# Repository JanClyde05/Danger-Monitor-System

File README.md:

# GPS Danger Monitor System – Full Code Documentation (v4.1)
##### BY: JAN CLYDE T. TALOSIG
##### **NEW IN v4.1: Physical Button Two-State Toggle + GPS Share / Open in Maps**
##### **NEW IN v4.0: Physical Disarm Button + False Alarm NRF Broadcast**
##### **NEW IN v3.x / Web Portal: Confirmed Accident Database + Diagnosis Notes + SOS Audio**

---

# 1. SYSTEM OVERVIEW

## 1.1 Purpose

The system is a **wearable/embedded safety monitor** that detects:

* Human falls (high confidence – three-stage FSM)
* Skid / slide events (lateral acceleration + roll rate)
* Direct high-G impacts (no freefall precondition)
* Environmental hazards (ground shock / structural instability / wave motion)

It then:

1. Gets GPS coordinates (last-known-location strategy)
2. Sends them via NRF24L01 with a token-prefixed payload
3. Triggers an SOS alert (LED + buzzer, Morse SOS pattern)
4. Opens a **web-based emergency profile with QR code quick-dial** via HID receiver
5. Allows the user to **cancel a false alarm** via physical button or web dashboard, which broadcasts a `FA,TOKEN,LAT,LNG` NRF packet to notify the receiver

---

## 1.2 System Components

### Transmitter (ESP32) – v4.1

* Sensors:
  * MPU-6050 (motion / orientation)
  * GPS module via TinyGPS++ (UART1, RX=16, TX=17)
* Communication:
  * NRF24L01 (wireless, CE=2, CSN=15)
* Interface:
  * Web dashboard in AP mode (three tabs: Monitor, Diagnostics, Simulation)
  * Physical disarm/re-arm button on GPIO 0 (BOOT button)

### Receiver (Pro Micro) – v2.3

* NRF24L01 (receiver, CE=9, CSN=10)
* HID Keyboard emulation (opens Netlify URL in browser)
* Handles three payload types: EMERGENCY, TEST, FALSE ALARM

### Web Layer

* ESP32 embedded dashboard (AP mode, 192.168.4.1)
* Netlify emergency portal (multi-page SPA with router)

---

# 2. ABSTRACT PROGRAM FLOW (SUMMARY)

## HIGH-LEVEL FLOW

```
BOOT → INIT HARDWARE → CALIBRATION → RUN LOOP
         ↓
     READ SENSORS (IMU + GPS)
         ↓
    APPLY SIM OVERRIDE (if drill mode)
         ↓
  UPDATE FALL-IMPACT-STILLNESS FSM
         ↓
  CHECK SKID / DIRECT IMPACT DETECTORS
         ↓
  CHECK ENVIRONMENTAL ANALYSIS (every 1 s)
         ↓
  SEND NRF ALERT + SOS (if triggered)
         ↓
  POLL PHYSICAL BUTTON (two-state toggle)
         ↓
  UPDATE WEB UI + BURST TEST (non-blocking)
         ↓
       REPEAT
```

---

## CORE LOGIC PIPELINES

### FALL DETECTION PIPELINE

```
[FS_IDLE]
   ↓ A_m < 0.40 g
[FS_FREEFALL]
   ↓ sustained ≥ 100 ms
[FS_WAIT_IMPACT]
   ↓ A_m > 3.00 g within 500 ms
[FS_STILLNESS]
   ↓ σ(A_m) < 0.15 g over 2 s
[FS_CONFIRMED → ALERT]
```

All stages must pass — eliminates false positives from jumping, device drops, or sleeping.

---

### SECONDARY DETECTORS (Parallel to FSM)

```
SKID / SLIDE:
  ay > 2.0 g  AND  gx > 330 °/s  sustained ≥ 200 ms
  → Ref: motorcycle crash paper, 96% accuracy

DIRECT IMPACT:
  A_m spike > 4.50 g  (no freefall precondition)
  5 s debounce between events
  → Ref: construction-site LF falls 4–9 g (Sensors 2022)
```

---

### EMERGENCY RESPONSE PIPELINE

```
[ACCIDENT DETECTED]
   ↓
[NRF PAYLOAD: "TOKEN,LAT,LNG"]
   ↓
[RECEIVER HID TRIGGERS URL]
   ↓
[NETLIFY PROFILE PAGE OPENS]
   ↓
[MEDICAL INFO + QR CODE DISPLAYED]
   ↓
[RESPONDER SCANS QR → tel: DIALS CONTACT]
   ↓ (optional)
[RESPONDER CONFIRMS ACCIDENT → DATABASE ENTRY]
```

---

### FALSE ALARM CANCELLATION PIPELINE (v4.0+)

```
[ALERT ACTIVE]
   ↓ (user presses physical button OR web False Alarm button)
[stopSOSAlert() — LED/buzzer off]
   ↓
[nrfSendFalseAlarm(): "FA,TOKEN,LAT,LNG"]
   ↓
[RECEIVER HID TRIGGERS FALSE ALARM URL]
   ↓
[NETLIFY: green "USER IS SAFE" page]
   ↓
[RESCUER INFORMED — NO RESPONSE NEEDED]
```

---

# 3. DETAILED MODULE EXPLANATION

## 3.1 SETUP PHASE

```
setup():
  Start Serial (115200)
  Start GPS UART1 (9600 baud, RX=16, TX=17)
  Initialize I2C (Wire.begin)
  Wake MPU-6050 (write 0x00 to PWR_MGMT_1)
  Calibrate MPU (3 seconds, 200 samples)
  Record gpsSearchStart timestamp
  Start WiFi AP (SSID: "GPS Danger Monitor", open, IP: 192.168.4.1)
  Initialize NRF24 (CE=2, CSN=15, PA_HIGH, 32-byte payload)
  Register all WebServer routes
  Configure GPIO: LED (4), Buzzer (5), Button (0 INPUT_PULLUP)
```

---

## 3.2 MAIN LOOP STRUCTURE

```
loop():
  Compute delta time dt
  server.handleClient()
  Poll physical button (50 ms debounce, two-state toggle)
  Run NRF burst test step (non-blocking, if pending)
  Feed GPS bytes → TinyGPS++, update hasFix / lastLat / lastLng
  readMPU() → apply sim override → updateOrientation(dt)
  Compute A_m = sqrt(ax²+ay²+az²)
  pushEnvSample(A_m, roll, pitch)
  Run Fall-Impact-Stillness FSM (if armed)
  Run Skid detector (if armed, FSM idle)
  Run Direct-Impact detector (if armed, FSM idle, not in skid)
  Environmental analysis (every 1 s, if armed, not sim)
  Drive SOS pattern (non-blocking)
```

---

# 4. SENSOR PROCESSING

## 4.1 MPU DATA FLOW

```
Raw MPU Data → Bias Removal → Physical Units → Orientation Estimation
```

### readMPU()

* Reads 14 bytes from register 0x3B
* Extracts ax, ay, az (±2 g range → /16384) and gx, gy, gz (±250 °/s → /131)
* Subtracts calibration offsets

### calibrateMPU()

* 200 samples over CALIB_MS (3000 ms)
* Averages each axis; subtracts 1.0 g from az bias (gravity)
* Stores: aBiasX/Y/Z, gBiasX/Y/Z

### updateOrientation(dt)

Complementary filter (α = 0.02):

```
aRoll  = atan2(ay, az) × 57.296°
aPitch = atan2(-ax, √(ay²+az²)) × 57.296°

roll  = (1-α)×(roll  + gx×dt) + α×aRoll
pitch = (1-α)×(pitch + gy×dt) + α×aPitch
```

## 4.2 ACCELERATION MAGNITUDE

```
A_m = sqrt(ax² + ay² + az²)
```

Orientation-independent scalar used by all detection stages.

---

# 5. FALL DETECTION STATE MACHINE

## States

| State           | Meaning                           |
|-----------------|-----------------------------------|
| FS_IDLE         | Normal monitoring                 |
| FS_FREEFALL     | Low-gravity condition detected    |
| FS_WAIT_IMPACT  | Waiting for impact spike          |
| FS_STILLNESS    | Verifying post-impact unconscious |
| FS_CONFIRMED    | Alert triggered                   |

## Full Flowchart

```
FS_IDLE
  IF A_m < 0.40 g → FS_FREEFALL, start timer

FS_FREEFALL
  IF A_m ≥ 0.40 g → back to FS_IDLE (false trigger)
  IF duration ≥ 100 ms → FS_WAIT_IMPACT
    Record fallStartMs, increment fallEventCount

FS_WAIT_IMPACT
  IF A_m > 3.00 g → FS_STILLNESS, reset stillness buffer
  IF timeout > 500 ms → FS_IDLE, increment fallCancelCount

FS_STILLNESS
  Collect samples for 2000 ms
  Compute σ(A_m)
  IF σ < 0.15 g → FS_CONFIRMED
  ELSE          → FS_IDLE (user conscious), increment fallCancelCount

FS_CONFIRMED
  Increment fallConfirmCount
  Log response time (now − fallStartMs)
  IF !simMode → nrfSendCoords(lastLat, lastLng, "Fall confirmed")
  ELSE        → nrfSendTest(99, "SIMFALL")
  startSOSAlert()
  → FS_IDLE
```

## Why This Works (Thesis Logic)

* Freefall alone → jumping false positive
* Impact alone → dropping the device
* Stillness alone → user sleeping
* **Combination of all three = confirmed real accident**

---

# 6. SECONDARY DETECTORS

## 6.1 Skid / Slide Detector

Active when: `armed == true` AND `fallState == FS_IDLE`

```
Condition: fabsf(ay) > 2.0 g  AND  fabsf(gx) > 330 °/s

If condition holds:
  Start skid timer on first detection
  If sustained ≥ 200 ms:
    skidCount++
    nrfSendCoords() OR nrfSendTest (sim)
    startSOSAlert()
    inSkid = false (reset)

If condition breaks before 200 ms:
  inSkid = false (cancel)
```

Reference: motorcycle crash paper, lateral 0.70 g + roll rate criteria, 96% accuracy.
*(Note: firmware thresholds are set higher — 2.0 g / 330 °/s — for reduced false positives in the specific deployment scenario.)*

---

## 6.2 Direct Impact Detector

Active when: `armed == true` AND `fallState == FS_IDLE` AND `!inSkid`

```
Condition: A_m > 4.50 g  AND  (now − lastImpactAlert) > 5000 ms

  lastImpactAlert = now
  impactCount++
  nrfSendCoords() OR nrfSendTest (sim)
  startSOSAlert()
```

Reference: Sensors 2022 — low-floor fall studies, 4–9 g impact range.

---

## 6.3 Environmental / Structural Instability

Runs every 1000 ms using the last `bufCount` samples from the rolling buffer (max 50).

```
sMag   = stddev(magBuf)
sRoll  = stddev(rollBuf)
sPitch = stddev(pitchBuf)

groundShock:  sMag ≥ 0.40  AND  sRoll < 10.0  AND  sPitch < 10.0
waveMotion:   sMag ≥ 0.24  AND  (sRoll ≥ 10.0 OR sPitch ≥ 10.0)

IF groundShock → nrfSendCoords("Ground shock")   + startSOSAlert()
IF waveMotion  → nrfSendCoords("Wave motion")     + startSOSAlert()
```

*(Environmental analysis is suppressed during simulation mode.)*

---

# 7. PHYSICAL BUTTON – TWO-STATE TOGGLE (v4.1)

**Pin:** GPIO 0 (BOOT button). Active-low with INPUT_PULLUP. 50 ms debounce on falling edge.

```
State A — alertActive = true:
  Press → armed = false
         stopSOSAlert()
         nrfSendFalseAlarm()   ← broadcasts "FA,TOKEN,LAT,LNG"
         lastEvent = "PHYSICAL DISARM – false alarm NRF sent/failed"

State B — armed = false (device was disarmed):
  Press → armed = true
         fallState = FS_IDLE
         inSkid = false
         lastEvent = "Re-armed via physical button"

Ignored — armed = true, alertActive = false:
  (Nothing to cancel — press is silently ignored)
```

---

# 8. NRF COMMUNICATION

## 8.1 Payload Formats (v4.1)

| Type           | Format                        | Example                              |
|----------------|-------------------------------|--------------------------------------|
| EMERGENCY      | `TOKEN,LAT,LNG`               | `DM-001,14.599512,120.984222`        |
| FALSE ALARM    | `FA,TOKEN,LAT,LNG`            | `FA,DM-001,14.5995,120.9842`         |
| TEST (burst/sim)| `TEST,NN,<tag>`              | `TEST,01,SIMFALL`                    |

All payloads are 32 bytes (NRF_PAYLOAD). Lat/Lng precision is 6 decimal places for EMERGENCY, 4 decimal places for FALSE ALARM (to fit within the 32-byte limit alongside the `FA,` prefix and token).

**Known hardware constraint:** IMU readings (ax, ay, gx) are NOT included in the FALSE ALARM payload. The 32-byte capacity is fully occupied by token + GPS coordinates. The Netlify portal displays "—" for IMU fields on the false alarm page and explicitly notes this constraint.

---

## 8.2 NRF Send Functions

### nrfSendCoords(lat, lng, reason)
* Formats `TOKEN,LAT,LNG` into a 32-byte buffer
* Calls `radio.write()`
* Updates `lastEvent`

### nrfSendFalseAlarm()
* Formats `FA,TOKEN,LAT,LNG` (4-decimal precision)
* Calls `radio.write()`
* Returns bool success

### nrfSendTest(seq, tag)
* Formats `TEST,NN,<tag>` (used by burst test and simulation drills)
* Prevents real emergency alerts during drill mode

---

## 8.3 NRF Hardware Config

| Parameter    | Value                  |
|--------------|------------------------|
| CE Pin       | GPIO 2                 |
| CSN Pin      | GPIO 15                |
| MOSI/MISO/SCK| 23 / 19 / 18           |
| Address      | 0xE8E8F0F01LL          |
| Payload size | 32 bytes               |
| PA Level     | RF24_PA_HIGH           |
| Mode         | TX (transmitter only)  |

---

# 9. WEB SERVER + DASHBOARD (ESP32)

## 9.1 Endpoints

| Route                  | Function                                              |
|------------------------|-------------------------------------------------------|
| `/`                    | Serves full dashboard HTML (three tabs)               |
| `/status.json`         | Live sensor data (armed, alertActive, GPS, IMU, fall state, sim) |
| `/diag-stats.json`     | GPS fix stats, fall event counters, burst state       |
| `/burst-results.json`  | 20-shot burst test results per packet                 |
| `/arm`                 | Set armed = true                                      |
| `/disarm`              | Set armed = false, stop SOS; if alertActive → send FA NRF |
| `/false-alarm`         | Manual FA: only works when alertActive; sends FA NRF  |
| `/test-nrf`            | Single legacy NRF test packet                         |
| `/run-burst`           | Start 20-packet burst test (non-blocking)             |
| `/simulate?event=X`    | Start simulation (skid / fall / impact)               |
| `/sim-stop`            | Stop simulation, reset IMU to idle state              |

## 9.2 /status.json Fields

```json
{
  "armed":       true,
  "alertActive": false,
  "hasFix":      true,
  "lat":         14.599512,
  "lng":         120.984222,
  "roll":        2.30,
  "pitch":      -1.20,
  "aMag":        1.023,
  "ay":          0.012,
  "gx":          0.5,
  "nrfReady":    true,
  "fallState":   0,
  "simEvent":    0,
  "inSkid":      false,
  "lastEvent":   "System boot"
}
```

## 9.3 Dashboard Tabs

### Monitor Tab
* **Alert Active Banner** — animated red banner shown when `alertActive = true`; includes hint about physical button and False Alarm button
* **System Controls** — Arm, Disarm, False Alarm (disabled when no active alert), NRF Single Test
* **Live Sensor Data** — 11 KV tiles: Armed, Alert Active, GPS Fix, Lat, Lng, Roll, Pitch, |A|, A-Y lateral, GX roll rate, NRF24 status
* **Fall Pipeline Bar** — color-coded progress bar across 5 FSM stages
* **GPS Location Actions** (v4.1 new):
  * **Share Location** button — copies `https://www.google.com/maps?q=LAT,LNG` to clipboard; disabled until valid GPS fix
  * **Open in Maps** button — opens Google Maps pin in new browser tab; disabled until valid GPS fix
  * GPS coordinate display below buttons (green when fix acquired)
* **Last Event** — monospace event log display
* **Detection Thresholds Reference** — literature-backed threshold summary with physical button behavior note

### Diagnostics Tab
* **NRF Burst Test** — 20-shot burst with per-packet ACK/FAIL status, latency bar, summary stats (success rate, avg/min/max delay)
* **GPS Fix Statistics** — fix count, average time-to-fix, current fix status
* **Fall Detection Diagnostics** — events detected, confirmed alerts, cancelled events, avg response time, precision rate, skid count, direct impact count

### Simulation Tab
* **Event Buttons** — Simulate Skid (SIM_SKID), Simulate Fall (SIM_FALL), Simulate Impact (SIM_IMPACT), Stop Sim
* **Sim Status Display** — live status string from `lastEvent`
* **IMU Threshold Reference Table** — literature-backed thresholds with event name, value, condition, and source
* **Live IMU Waveform Canvas** — rolling 80-sample aMag plot with threshold lines (freefall 0.40 g, skid 0.70 g, impact 3.00 g, direct 4.00 g)

---

# 10. IMU SIMULATION MODE

Three simulation events inject synthetic IMU waveforms to test the detection pipeline end-to-end without physically triggering the device.

### SIM_SKID (~700 ms)
* Sine-enveloped lateral ay peak ~0.85 g + gx peak ~55 °/s
* Designed to cross SKID_LATERAL_G and SKID_ROLL_RATE thresholds
* Sends `nrfSendTest(98, "SIMSKID")` instead of real alert

### SIM_FALL (~2650 ms)
```
0–100 ms  : Pre-fall lean (az drops, gx rises)
100–280 ms: Freefall (A_m ≈ 0.18 g — well below 0.40 g threshold)
280–330 ms: Impact spike (A_m ≈ 4.8 g — above 3.00 g threshold)
330–2650 ms: Stillness (σ < 0.05 g — below 0.15 g threshold)
```
* Sends `nrfSendTest(99, "SIMFALL")`

### SIM_IMPACT (~200 ms)
* Gaussian impulse: peak A_m ≈ 4.8 g (above IMPACT_DIRECT_G = 4.50 g)
* Sends `nrfSendTest(97, "SIMIMPACT")`

All simulations set `lastEvent` with drill status and suppress real NRF emergency packets.

---

# 11. RECEIVER (PRO MICRO) – v2.3

## 11.1 Three Payload Types

```
WAIT for NRF packet (radio.available())
   ↓
Read 32-byte payload → String raw
   ↓
Detect type:
  raw.startsWith("TEST,")  → TEST handler
  raw.startsWith("FA,")    → FALSE ALARM handler
  else                     → EMERGENCY handler
```

## 11.2 EMERGENCY Handler

```
Parse: TOKEN = raw[0..c1], COORDS = raw[c1+1..]
Build URL: https://danger-monitor-profile.netlify.app/?token=TOKEN&loc=LAT,LNG
Debounce: 1500 ms between triggers
openURL(url) → HID keyboard simulation
```

## 11.3 FALSE ALARM Handler (v2.3 New)

```
Parse: FA | TOKEN | LAT | LNG
Build URL: https://danger-monitor-profile.netlify.app/?falarm=1&token=TOKEN&loc=LAT,LNG
Debounce: 1500 ms
openURL(url) → HID keyboard simulation
```
→ Netlify displays **green "USER IS SAFE" page** instead of emergency profile.

## 11.4 TEST Handler

```
Parse seq number from "TEST,NN,tag"
Build URL: https://danger-monitor-profile.netlify.app/?nrftest=1&seq=NN&ts=millis
Debounce: 1500 ms
openURL(url)
```
→ Netlify shows a toast notification and stays on home page.

## 11.5 openURL() – HID Sequence

```
Keyboard.press(Ctrl + L)   → focus address bar
Keyboard.releaseAll()
delay(250)
Keyboard.press(Ctrl + A)   → select existing URL
Keyboard.releaseAll()
delay(80)
Keyboard.print(url)        → type new URL
delay(80)
Keyboard.write(KEY_RETURN) → navigate
```

## 11.6 Wiring

| NRF24 Pin | Pro Micro Pin |
|-----------|---------------|
| CE        | 9             |
| CSN       | 10            |
| MOSI      | 16 (MOSI)     |
| MISO      | 14 (MISO)     |
| SCK       | 15 (SCK)      |
| VCC       | 3.3 V only    |

---

# 12. NETLIFY EMERGENCY PORTAL (Web Layer)

## 12.1 Technology Stack

```
HTML5 / CSS3 / Vanilla JavaScript
QRCode.js (CDN: cdnjs.cloudflare.com)
localStorage (Confirmed Accident Database)
Web Audio API (SOS sound engine)
No backend required — fully static
```

## 12.2 URL Router

The portal reads URL parameters on load and routes to the correct page:

| URL Pattern                                          | Page Shown              |
|------------------------------------------------------|-------------------------|
| `/` (no params)                                      | Home – Device Grid      |
| `/?token=DM-001&loc=14.599,120.984`                  | Emergency Profile       |
| `/?falarm=1&token=DM-001&loc=14.5995,120.9842`       | False Alarm – Safe Page |
| `/?nrftest=1&seq=NN&ts=...`                          | Home + toast            |
| `/?loc=14.599,120.984` (no token)                    | First profile (legacy)  |
| `/?token=DM-XXX` (unknown token)                     | Token Not Found page    |

## 12.3 Pages

### Home Page
* Hero section: system description, stats (device count, repeater spacing, RF protocol)
* **Device Grid** — card per profile showing avatar, name, role, token, blood type, contact
* Clicking any card opens that profile's Emergency Profile view

### Emergency Profile Page
* **Alert Banner** — animated red pulsing banner with SOS mute toggle button
* **Audio Unlock Bar** — shown on mobile when autoplay is blocked; tap to enable SOS alarm
* **Medical Profile Card** — avatar, name, role, token, blood type, allergies, emergency contact, medical notes
* **QR Code Section** — auto-generated `tel:` QR code for instant emergency contact dial
* **Location Card** — live coordinates, Google Maps button (hidden if no location)
* **Rescuer Action Row**:
  * **Share Alert** — copies current emergency URL to clipboard
  * **Confirm Accident** — opens token-confirmation modal; logs entry to Confirmed Accident Database
* Back button → Home

### False Alarm Page
* **Safe Banner** — green pulsing "USER IS SAFE" banner
* **Safe Status Row** — green indicator dot + "DEVICE OWNER CONFIRMED SAFE" text
* **Profile Card (green border)** — same medical info as emergency profile
* **IMU Readings at Disarm** — displays "—" for all three fields with hardware constraint note
* **Location Card** — last-known GPS position

### Confirmed Accident Database Page
* Header with record count and Clear All button
* Per-entry cards showing: avatar, name, token, confirmed timestamp, coordinates (Maps link), medical summary
* **Medical Diagnosis Notes** — collapsible section per accident:
  * Add Text Note (textarea)
  * Add Image (file input → base64)
  * Attach File (file input → base64 data URL)
  * Delete individual notes
* **Delete Accident Record** — per-card ✕ button; requires token confirmation via modal
* Empty state placeholder when no records

### Token Not Found Page
* Shows the unrecognized token string
* Back button → Home

## 12.4 Token Confirmation Modal

Used for both "Confirm Accident" and "Delete Record" actions.

```
openModal({
  mode:  'confirm' | 'delete',
  token: required token string,
  onOk:  callback on success
})
```

* User must type the device token exactly (case-insensitive) to unlock the OK button
* Input highlights green on match; button label differs by mode ("Log to Database" vs "Delete")
* Dismiss via Cancel button, backdrop click, or Escape key

## 12.5 QR Code System

```javascript
generateQRCode(phoneNumber, containerId)
  telLink = 'tel:' + phoneNumber.replace(/\s/g, '')
  new QRCode(container, {
    text:         telLink,
    width:        200, height: 200,
    colorDark:    '#000000',
    colorLight:   '#ffffff',
    correctLevel: QRCode.CorrectLevel.H   // 30% error recovery
  })
```

| Property        | Value                  |
|-----------------|------------------------|
| Encoding        | `tel:` URI protocol    |
| Size            | 200 × 200 px           |
| Error Correction| Level H (30% recovery) |
| Generation      | Client-side (instant)  |
| Offline support | Yes (no network needed)|

## 12.6 SOS Audio Engine

Non-blocking Morse SOS pattern using Web Audio API:

```
Pattern: ... --- ...  (dot=80ms, dash=240ms, gap=80ms, long gap=240ms, word gap=560ms)
Tone:    880 Hz sine wave, gain 0.35
```

* `SOS.tryAutoplay()` — called on profile load; shows unlock bar if browser blocks autoplay
* `SOS.start()` / `SOS.stop()` — start/stop the oscillator pattern loop
* `SOS.toggleMute()` — mute/unmute without stopping the pattern timer
* SOS is always stopped when navigating to False Alarm page or Home

## 12.7 Confirmed Accident Database (localStorage)

```
Key: 'dm_accidents'
Schema per entry:
{
  id:          string (timestamp),
  confirmedAt: ISO date string,
  token:       "DM-XXX",
  profile:     { ...snapshot of profile at time of confirmation },
  loc:         "LAT,LNG" or "",
  url:         full emergency URL,
  diagNotes:   [
    {
      id:       string,
      addedAt:  ISO date string,
      type:     "text" | "image" | "file",
      content:  text string | base64 data URL,
      fileName: string,
      mimeType: string
    }
  ]
}
```

Entries are stored newest-first. Image and file notes are stored as base64 data URLs. A 2 MB per-file warning prompt is shown to prevent exceeding localStorage limits (~5–10 MB per origin).

## 12.8 Registered Profiles

```javascript
const PROFILES = [
  { token: "DM-001", name: "Jan Clyde Talosig",     blood: "B+",  allergies: "None",          ... },
  { token: "DM-002", name: "James Laurence Guzman", blood: "O+",  allergies: "Skin Allergies", ... },
  { token: "DM-003", name: "Kaye Angelique Aquino", blood: "A+",  allergies: "None",           ... },
  { token: "DM-004", name: "Shamel Alliyah Senson", blood: "AB+", allergies: "None",           ... },
  { token: "DM-005", name: "Zarina Marie Aguilar",  blood: "AB+", allergies: "None",
    notes: "Have history of heart complications"                                                  },
];
```

To add a new device, append a new object to the `PROFILES` array in `emergency_portal_qr.html`.

---

# 13. SOS ALERT SYSTEM

## Pattern

Morse Code SOS: `... --- ...` (non-blocking)

```javascript
const SOS_STEPS = [
  {on:true,ms:150},{on:false,ms:150},  // S dot 1
  {on:true,ms:150},{on:false,ms:150},  // S dot 2
  {on:true,ms:150},{on:false,ms:150},  // S dot 3
  {on:true,ms:450},{on:false,ms:150},  // O dash 1
  {on:true,ms:450},{on:false,ms:150},  // O dash 2
  {on:true,ms:450},{on:false,ms:150},  // O dash 3
  {on:true,ms:150},{on:false,ms:150},  // S dot 1
  {on:true,ms:150},{on:false,ms:150},  // S dot 2
  {on:true,ms:150},{on:false,ms:600},  // S dot 3 + word gap
];
```

* LED (GPIO 4) and Buzzer (GPIO 5, 3000 Hz) toggled in sync
* `startSOSAlert()` — sets `alertActive = true`, starts pattern
* `stopSOSAlert()` — sets `alertActive = false`, turns off LED and buzzer
* Pattern cycles with `millis()` timing — does not block the main loop

---

# 14. GPS HANDLING

## Strategy: Last-Known Location

```
IF GPS valid:
    update lastLat, lastLng
    IF first fix after search: record fix time, increment gpsFixCount
ELSE:
    keep last valid coordinates (lastLat, lastLng)

IF fix age > 8000 ms:
    hasFix = false → start searching
```

## GPS Diagnostics

Tracked in firmware and exposed via `/diag-stats.json`:
* `gpsFixCount` — number of times a fix was (re-)acquired
* `gpsTotalFixMs` — cumulative time-to-fix; divide by count for average
* `gpsSearchStart` — timestamp of last fix-lost event

---

# 15. SYSTEM STATES

## Armed Mode (`armed = true`)

* All detection FSMs active (fall, skid, direct impact, environmental)
* SOS alerts allowed
* NRF broadcasting enabled
* Physical button in State A/Ignored logic

## Disarmed Mode (`armed = false`)

* All FSMs reset to idle
* SOS stopped
* NRF dormant
* Physical button in State B (re-arm) logic

## Alert Active (`alertActive = true`)

* Subset of armed mode — a confirmed event is in progress
* SOS LED/buzzer cycling
* Web dashboard shows animated red banner
* False Alarm button enabled
* Physical button triggers disarm + FA NRF

---

# 16. KEY VARIABLES YOU CAN MODIFY

## Detection Thresholds

```cpp
// Fall-Impact-Stillness
FREEFALL_G        = 0.40f    // g — below this triggers freefall
IMPACT_G          = 3.00f    // g — above this after freefall = impact
STILLNESS_STD_MAX = 0.15f    // g σ — below this = unconscious
FREEFALL_DUR_MS   = 100      // ms — min freefall duration
IMPACT_WINDOW_MS  = 500      // ms — impact must occur within this window
STILLNESS_DUR_MS  = 2000     // ms — stillness observation window

// Skid
SKID_LATERAL_G    = 2.0f     // g — lateral ay threshold
SKID_ROLL_RATE    = 330.0f   // °/s — gx roll rate threshold
SKID_DUR_MS       = 200      // ms — sustained duration

// Direct Impact
IMPACT_DIRECT_G   = 4.50f    // g — spike threshold
IMPACT_DEBOUNCE   = 5000     // ms — minimum time between direct impact alerts

// Environmental
ACC_STD_DANGER    = 0.40f    // g σ — acceleration variance threshold
ROLL_PITCH_STD    = 10.0f    // ° σ — orientation variance threshold
ANALYZE_EVERY_MS  = 1000     // ms — analysis interval
```

## Hardware Pins

```cpp
GPS_RX = 16, GPS_TX = 17, GPS_BAUD = 9600
MPU_ADDR = 0x68 (I2C, SDA=21, SCL=22)
NRF_CE = 2, NRF_CSN = 15
ALERT_LED_PIN = 4
BUZZER_PIN = 5
DISARM_BTN_PIN = 0
```

## Device Token

```cpp
const char* DEVICE_TOKEN = "DM-001";
```

Each physical device must have a unique token matching an entry in the `PROFILES` array.

---

# 17. FULL SYSTEM ARCHITECTURE

## v4.1 Block Diagram

```
[MPU6050] ──┐
            ├─→ ESP32 ─→ FALL / SKID / IMPACT FSMs ─→ NRF24 ──┐
[GPS]    ───┘      ↓              ↓                            │
                SOS ALERT   Physical BTN (GPIO 0)              │
               (LED/Buzz)    ↓ (if alertActive)                │
                         FA NRF packet ──────────────────────  │
                                                               ↓
                                                          Pro Micro
                                                               ↓
                                                 HID Keyboard Emulation
                                                               ↓
                                              Browser → Netlify Portal
                                                               ↓
                                         ┌──────────────────────────────┐
                                         │  Emergency Profile + QR      │
                                         │  OR False Alarm Safe Page    │
                                         │  OR Test Toast Notification  │
                                         └──────────────────────────────┘
                                                               ↓
                                                  Responder Scans QR
                                                               ↓
                                                   Phone Auto-Dials
                                                               ↓
                                           (optional) Confirm Accident
                                                               ↓
                                              Accident Database Entry
                                                               ↓
                                          Medical Personnel Adds Notes
```

---

## Data Flow – Emergency Scenario

```
TRANSMITTER (ESP32):
  Fall / Skid / Impact Detected
       ↓
  GPS: lastLat, lastLng
       ↓
  Payload: "DM-001,14.599512,120.984222"
       ↓
  NRF24 → radio.write()
       ↓
  SOS LED + Buzzer activated

RECEIVER (Pro Micro):
  radio.available() → radio.read()
       ↓
  Payload type: EMERGENCY (no "FA," prefix, no "TEST," prefix)
       ↓
  Parse: token="DM-001", coords="14.599512,120.984222"
       ↓
  URL: https://danger-monitor-profile.netlify.app/?token=DM-001&loc=14.599512,120.984222
       ↓
  HID: Ctrl+L → Ctrl+A → type URL → Enter

NETLIFY PORTAL:
  route() reads params
       ↓
  PROFILES.find(token === "DM-001")
       ↓
  renderProfile(profile, "14.599512,120.984222")
       ↓
  Display: photo, name, blood type, allergies, contact, notes
  Generate: QR code (tel:+63917XXXXXX)
  Show:     Google Maps link
  Play:     SOS audio (880 Hz Morse pattern)
       ↓
  Responder scans QR → phone dials contact
  (optional) Rescuer clicks "Confirm Accident" → enters token → logs to DB
```

---

## Data Flow – False Alarm Scenario

```
TRANSMITTER (ESP32):
  User presses GPIO 0 while alertActive = true
       ↓
  stopSOSAlert() — LED/buzzer off
       ↓
  nrfSendFalseAlarm()
  Payload: "FA,DM-001,14.5995,120.9842"
       ↓
  armed = false

RECEIVER (Pro Micro):
  raw.startsWith("FA,") → FALSE ALARM handler
       ↓
  Parse: token="DM-001", loc="14.5995,120.9842"
       ↓
  URL: https://danger-monitor-profile.netlify.app/?falarm=1&token=DM-001&loc=14.5995,120.9842
       ↓
  HID: openURL()

NETLIFY PORTAL:
  route() detects falarm=1
       ↓
  renderFalseAlarm(profile, loc)
       ↓
  Green "USER IS SAFE" banner + profile info
  SOS audio stopped
  IMU fields show "—" (hardware constraint)
  Last known GPS position displayed
```

---

# 18. DEPLOYMENT CHECKLIST (v4.1)

## Transmitter Setup

- [ ] Program ESP32 with v4.1 firmware
- [ ] Set `DEVICE_TOKEN` to match Netlify `PROFILES` entry (e.g., `"DM-001"`)
- [ ] Configure WiFi AP SSID/password in `AP_SSID` / `AP_PASS`
- [ ] Set NRF24 channel and address to match receiver
- [ ] Calibrate MPU-6050 (hold device still during 3 s boot calibration)
- [ ] Test GPS fix (outdoor location, wait for `hasFix = true`)
- [ ] Verify SOS alert (LED + buzzer)
- [ ] Test physical button: arm → trigger alert → press button → verify FA NRF + disarm → press again → verify re-arm

## Receiver Setup

- [ ] Program Pro Micro with v2.3 firmware
- [ ] Configure NRF24 CE=9, CSN=10 to match transmitter address
- [ ] Test NRF pairing (LED blink on packet reception)
- [ ] Connect to PC via USB (HID driver auto-installs)
- [ ] Test keyboard emulation with a test payload

## Web Portal Setup

- [ ] Update `PROFILES` array with real names, photos, and contact numbers
- [ ] Deploy `emergency_portal_qr.html` to Netlify
- [ ] Test emergency URL: `?token=DM-001&loc=14.599,120.984`
- [ ] Test false alarm URL: `?falarm=1&token=DM-001&loc=14.5995,120.9842`
- [ ] Test NRF test URL: `?nrftest=1&seq=01&ts=12345`
- [ ] Verify QR code generation and mobile scan-to-dial
- [ ] Test Confirm Accident flow → Database entry → Diagnosis notes
- [ ] Test Delete Record flow with token confirmation
- [ ] Verify SOS audio on mobile (tap unlock bar if needed)

## Field Testing

- [ ] Controlled fall drill: use Simulate Fall on dashboard, verify FSM progression
- [ ] Skid drill: use Simulate Skid, verify NRF test packet sent
- [ ] Impact drill: use Simulate Impact, verify direct-impact alert
- [ ] Physical button false alarm test (step-by-step toggle)
- [ ] Web disarm false alarm test (dashboard button)
- [ ] NRF 20-shot burst test (check success rate ≥ 90%)
- [ ] GPS Share Location — copy link, verify coordinates
- [ ] GPS Open in Maps — verify correct pin location
- [ ] End-to-end: fall → NRF → browser opens profile → QR scan → call

---

# 19. VERSION COMPARISON

| Feature                        | v2.1        | v4.0           | v4.1                    |
|--------------------------------|-------------|----------------|-------------------------|
| Fall detection                 | FSM (3-stage)| FSM (3-stage) | FSM (3-stage)           |
| Skid detection                 | ✗           | ✓              | ✓                       |
| Direct impact detection        | ✗           | ✓              | ✓                       |
| Simulation drills              | ✗           | ✓              | ✓                       |
| NRF burst test                 | ✗           | ✓              | ✓                       |
| Physical disarm button         | ✗           | Single-press   | Two-state toggle        |
| Physical re-arm                | ✗           | ✗              | ✓ (second press)        |
| False alarm NRF packet         | ✗           | ✓              | ✓                       |
| False alarm Netlify page       | ✗           | ✗              | ✓ (green safe page)     |
| GPS Share Location button      | ✗           | ✗              | ✓                       |
| GPS Open in Maps button        | ✗           | ✗              | ✓                       |
| Multi-profile support          | Token-based | Token-based    | Token-based (5 profiles)|
| QR code quick-dial             | ✓           | ✓              | ✓                       |
| Confirmed accident database    | ✗           | ✗              | ✓ (localStorage)        |
| Medical diagnosis notes        | ✗           | ✗              | ✓ (text/image/file)     |
| SOS audio (browser)            | ✗           | ✗              | ✓ (Web Audio API)       |
| Alert Active indicator         | ✗           | ✓              | ✓                       |
| Dashboard tabs                 | 1           | 3              | 3                       |
| Receiver payload types         | 1           | 2              | 3 (EM + TEST + FA)      |

---

# 20. FINAL NOTES (v4.1)

✔ Non-blocking design throughout (SOS, burst test, button debounce, GPS feed)
✔ Multi-layer detection: Fall FSM + Skid + Direct Impact + Environmental
✔ Two-state physical button toggle: disarm+FA when alert active, re-arm when disarmed
✔ GPS Share and Open in Maps for rapid responder location relay
✔ Token-based routing with 5 registered device profiles
✔ Zero-installation responder workflow (browser-based Netlify portal)
✔ False alarm broadcast prevents unnecessary emergency response
✔ Confirmed accident database with full medical diagnosis notes system
✔ SOS audio engine with mobile autoplay unlock handling
✔ IMU simulation drills with realistic waveforms for pre-deployment testing
✔ Thesis-grade documentation with literature-backed detection thresholds

---

**Last Updated:** April 2026
**Firmware Versions:** ESP32 v4.1 | Pro Micro Receiver v2.3 | Netlify Portal v4.x
**Status:** Production Ready

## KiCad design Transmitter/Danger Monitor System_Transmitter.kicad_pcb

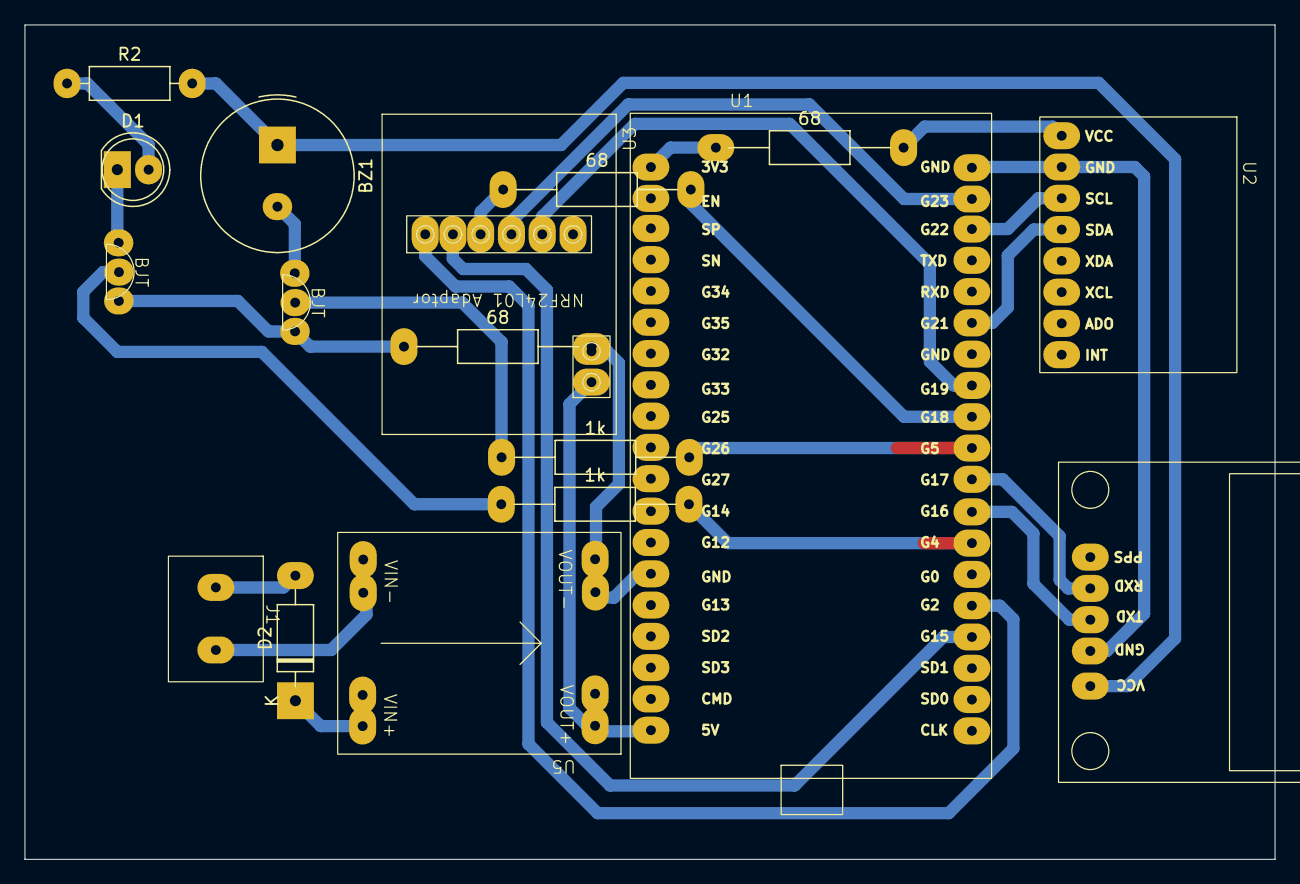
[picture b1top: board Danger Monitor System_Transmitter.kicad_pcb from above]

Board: 2 copper layers, 101.5 x 67.8 mm, 17 parts (0 on the bottom side), 22 nets.

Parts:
1k, 1k#2, 68, 68#2, 68#3: R_Axial_DIN0207_L6.3mm_D2.5mm_P15.24mm_Horizontal
BJT: 2N2222A
BJT#2: 2N2222A
BZ1: Buzzer; Buzzer_TDK_PS1240P02BT_D12.2mm_H6.5mm
D1: LED; LED_D5.0mm_Clear
D2: D; D_A-405_P10.16mm_Horizontal
J1: Screw_Terminal_01x02; Screw Terminal 2 Pin
R2: 1k; R_Axial_DIN0207_L6.3mm_D2.5mm_P10.16mm_Horizontal
U1: ESP-WROOM-32
U2: MPU-6050
U3: NRF24L01 Adaptor
U4: NEO7
U5: MP1584EN

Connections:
3V3: 68#3.1, 68#3.2, U1.1 (3V3), U2.1 (VCC)
5V: BZ1.1 (+), R2.2, U1.19 (5V), U3.7 (VCC), U4.1 (VCC), U5.1 (VIN+)
Buzzer Signal: 1k.2, U1.29 (G5)
CE: U1.24 (G2), U3.1 (CE)
CLK: 68.1, 68.2, U1.30 (G18), U3.3 (CLK)
CSN: U1.23 (G15), U3.2 (CSN)
GND: 68#2.1, 68#2.2, BJT.2, BJT#2.2, U1.14 (GND), U1.38 (GND), U2.2 (GND), U3.8 (GND), U4.2 (RX), U5.7
GND_IN: J1.2, U5.8
GPS RX: U1.28 (G17), U4.4 (GND)
GPS TX: U1.27 (G16), U4.3 (TX)
Light Signal: 1k#2.2, U1.26 (G4)
MISO: U1.31 (G19), U3.5 (MISO)
MOSI: U1.37 (G23), U3.4 (MOSI)
unnamed: BJT.3, BZ1.2 (-)
unnamed: D1.2 (A), R2.1
unnamed: BJT#2.3, D1.1 (K)
unnamed: D2.1 (K), U5.3 (VOUT+)
unnamed: 1k.1, BJT.1
unnamed: 1k#2.1, BJT#2.1
SCL: U1.36 (G22), U2.3 (SCL)
SDA: U1.33 (G21), U2.4 (SDA)
VCC: D2.2 (A), J1.1

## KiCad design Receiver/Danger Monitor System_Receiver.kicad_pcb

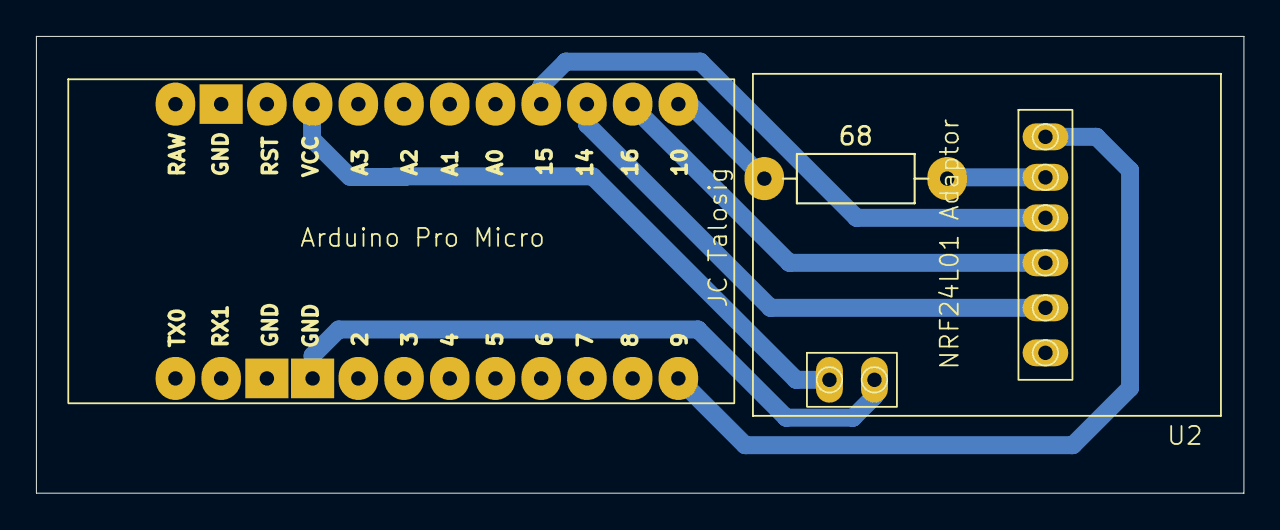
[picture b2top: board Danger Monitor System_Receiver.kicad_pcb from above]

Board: 2 copper layers, 67.1 x 25.4 mm, 3 parts (0 on the bottom side), 7 nets.

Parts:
68: R_Axial_DIN0207_L6.3mm_D2.5mm_P10.16mm_Horizontal
U1: Pro Micro
U2: NRF24L01 Adaptor

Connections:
CE: U1.12 (10), U2.1 (CE)
CLK: U1.16 (A0), U2.3 (CLK)
CSN: 68.1, 68.2, U1.13 (16), U2.2 (CSN)
GND: U1.3 (GND), U1.4 (GND), U1.22 (GND), U2.8 (GND)
MISO: U1.15, U2.5 (MISO)
MOSI: U1.14, U2.4 (MOSI)
VCC: U1.21 (RST), U2.7 (VCC)

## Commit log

2026-04-03 Initial commit - Danger Monitor System
2026-04-03 Revise README for SHM System full documentation
    Updated the README to provide comprehensive documentation for the Structural Health Monitoring System, including system overview, architecture, program flow, and detailed descriptions of tasks and fu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
2026-04-03 Initial commit V2
2026-04-03 Revise README for GPS Danger Monitor System v2.0
    Updated project documentation to reflect changes in system functionality and purpose.
2026-04-03 Updates lang here
2026-04-03 Update all project files
2026-04-03 Bug Fixed sa NRF
2026-04-04 Added some Docs
2026-04-09 Update README.md
    Added QR description
2026-04-11 Updates sa Web
2026-04-28 New Updates
2026-04-28 Update print statement from 'Hello' to 'Goodbye'
